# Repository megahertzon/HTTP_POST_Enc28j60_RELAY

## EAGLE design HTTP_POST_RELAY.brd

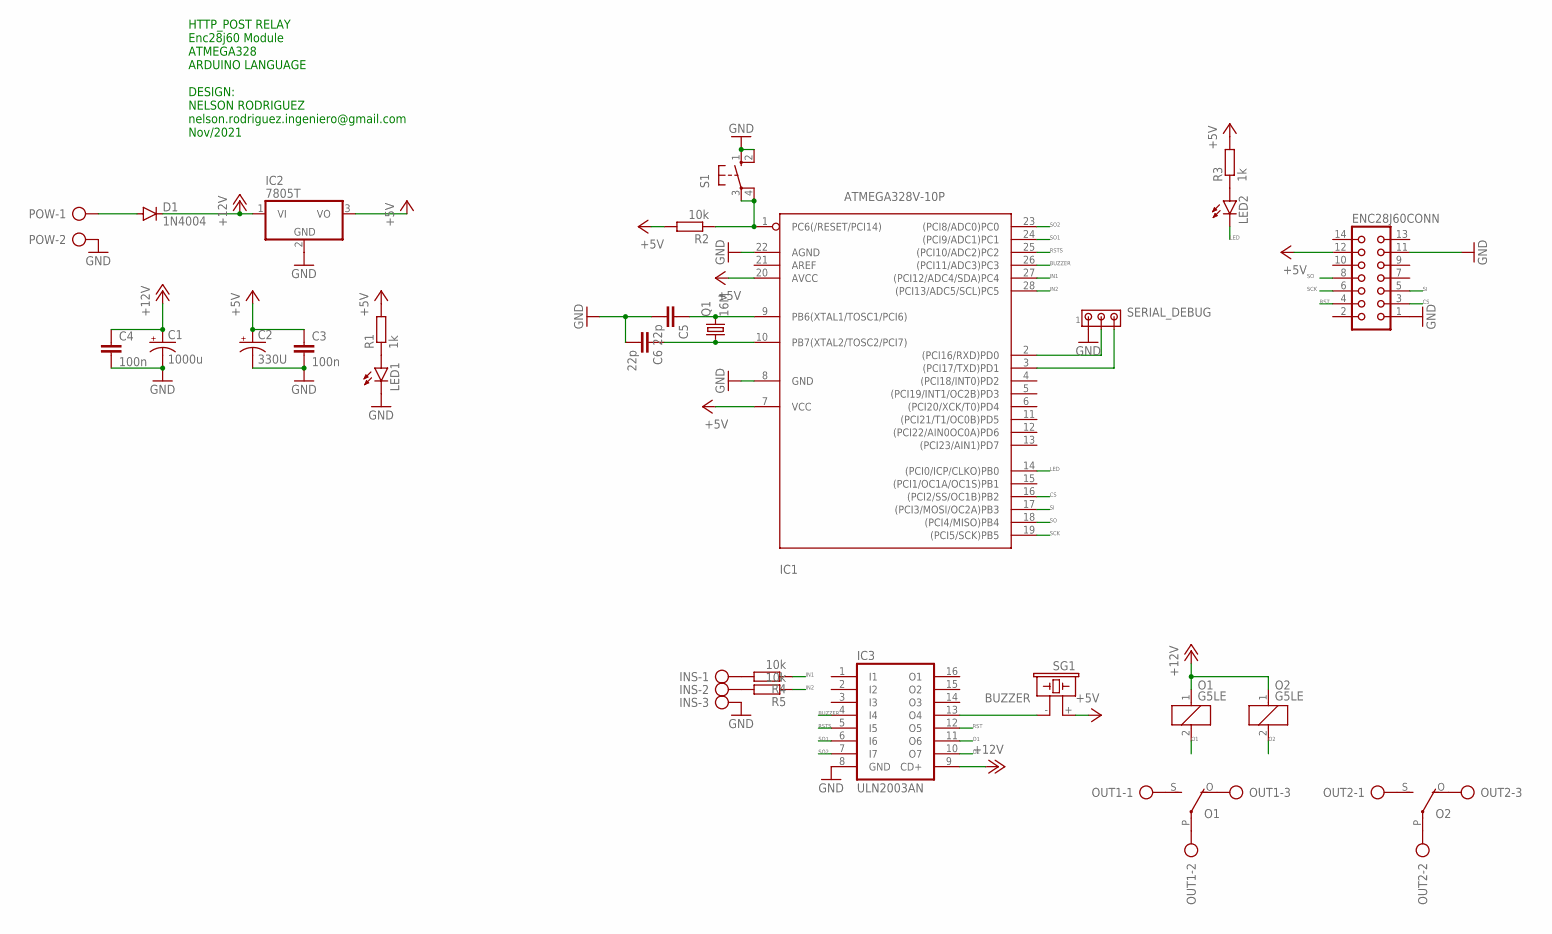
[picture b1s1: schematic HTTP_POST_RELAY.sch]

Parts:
C1: 1000u; E2,5-6
C2: 330U; E2,5-6
C3, C4: 100n; C025-024X044
C5, C6: 22p; C025-024X044
D1: 1N4004; DO41-10
ENC28J60CONN: CON14
IC1: ATMEGA328V-10P; DIL28-3
IC2: 7805T; TO220H
IC3: ULN2003AN; DIL16
INS: AK300/3
LED1, LED2: LED5MM
O1, O2: G5LE
OUT1, OUT2: AK300/3
POW: AK300/2
Q1: 16M; HC49U-V
R1, R3: 1k; 0204/7
R2, R4, R5: 10k; 0204/7
S1: 10-XX; B3F-10XX
SERIAL_DEBUG: MTA03-100; 10X03MTA
SG1: BUZZER; F/CM12P

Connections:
+5V: C2.+, C3.1, ENC28J60CONN.12, IC1.7 (VCC), IC1.20 (AVCC), IC2.3 (VO), R1.2, R2.2, R3.2, SG1.+ (1)
+12V: C1.+, C4.1, D1.C, IC2.1 (VI), IC3.9 (CD+), O1.1, O2.1
BUZZER: IC1.26 ((PCI11/ADC3)PC3), IC3.4 (I4)
CS: ENC28J60CONN.3, IC1.16 ((PCI2/SS/OC1B)PB2)
GND: C1.-, C2.-, C3.2, C4.2, C5.2, C6.2, ENC28J60CONN.1, ENC28J60CONN.11, IC1.8 (GND), IC1.22 (AGND), IC2.2 (GND), IC3.8 (GND), INS.3, LED1.K (C), POW.2, S1.1 (S), S1.2 (S1), SERIAL_DEBUG.1
IN1: IC1.27 ((PCI12/ADC4/SDA)PC4), R4.1
IN2: IC1.28 ((PCI13/ADC5/SCL)PC5), R5.1
LED: IC1.14 ((PCI0/ICP/CLKO)PB0), LED2.K (C)
unnamed: D1.A, POW.1
unnamed: LED1.A, R1.1
unnamed: C6.1, IC1.10 (PB7(XTAL2/TOSC2/PCI7)), Q1.1
unnamed: C5.1, IC1.9 (PB6(XTAL1/TOSC1/PCI6)), Q1.2
unnamed: IC1.2 ((PCI16/RXD)PD0), SERIAL_DEBUG.2
unnamed: IC1.1 (PC6(/RESET/PCI14)), R2.1, S1.3, S1.4 (P1)
unnamed: IC1.3 ((PCI17/TXD)PD1), SERIAL_DEBUG.3
unnamed: LED2.A, R3.1
unnamed: IC3.13 (O4), SG1.- (2)
unnamed: INS.1, R4.2
unnamed: INS.2, R5.2
unnamed: O1.P, OUT1.2
unnamed: O1.S, OUT1.1
unnamed: O1.O, OUT1.3
unnamed: O2.P, OUT2.2
unnamed: O2.S, OUT2.1
unnamed: O2.O, OUT2.3
O1: IC3.11 (O6), O1.2
O2: IC3.10 (O7), O2.2
RST: ENC28J60CONN.4, IC3.12 (O5)
RSTS: IC1.25 ((PCI10/ADC2)PC2), IC3.5 (I5)
SCK: ENC28J60CONN.6, IC1.19 ((PCI5/SCK)PB5)
SI: ENC28J60CONN.5, IC1.17 ((PCI3/MOSI/OC2A)PB3)
SO: ENC28J60CONN.8, IC1.18 ((PCI4/MISO)PB4)
SO1: IC1.24 ((PCI9/ADC1)PC1), IC3.6 (I6)
SO2: IC1.23 ((PCI8/ADC0)PC0), IC3.7 (I7)

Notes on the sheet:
HTTP_POST RELAY Enc28j60 Module ATMEGA328 ARDUINO LANGUAGE DESIGN: NELSON RODRIGUEZ nelson.rodriguez.ingeniero@gmail.com Nov/2021

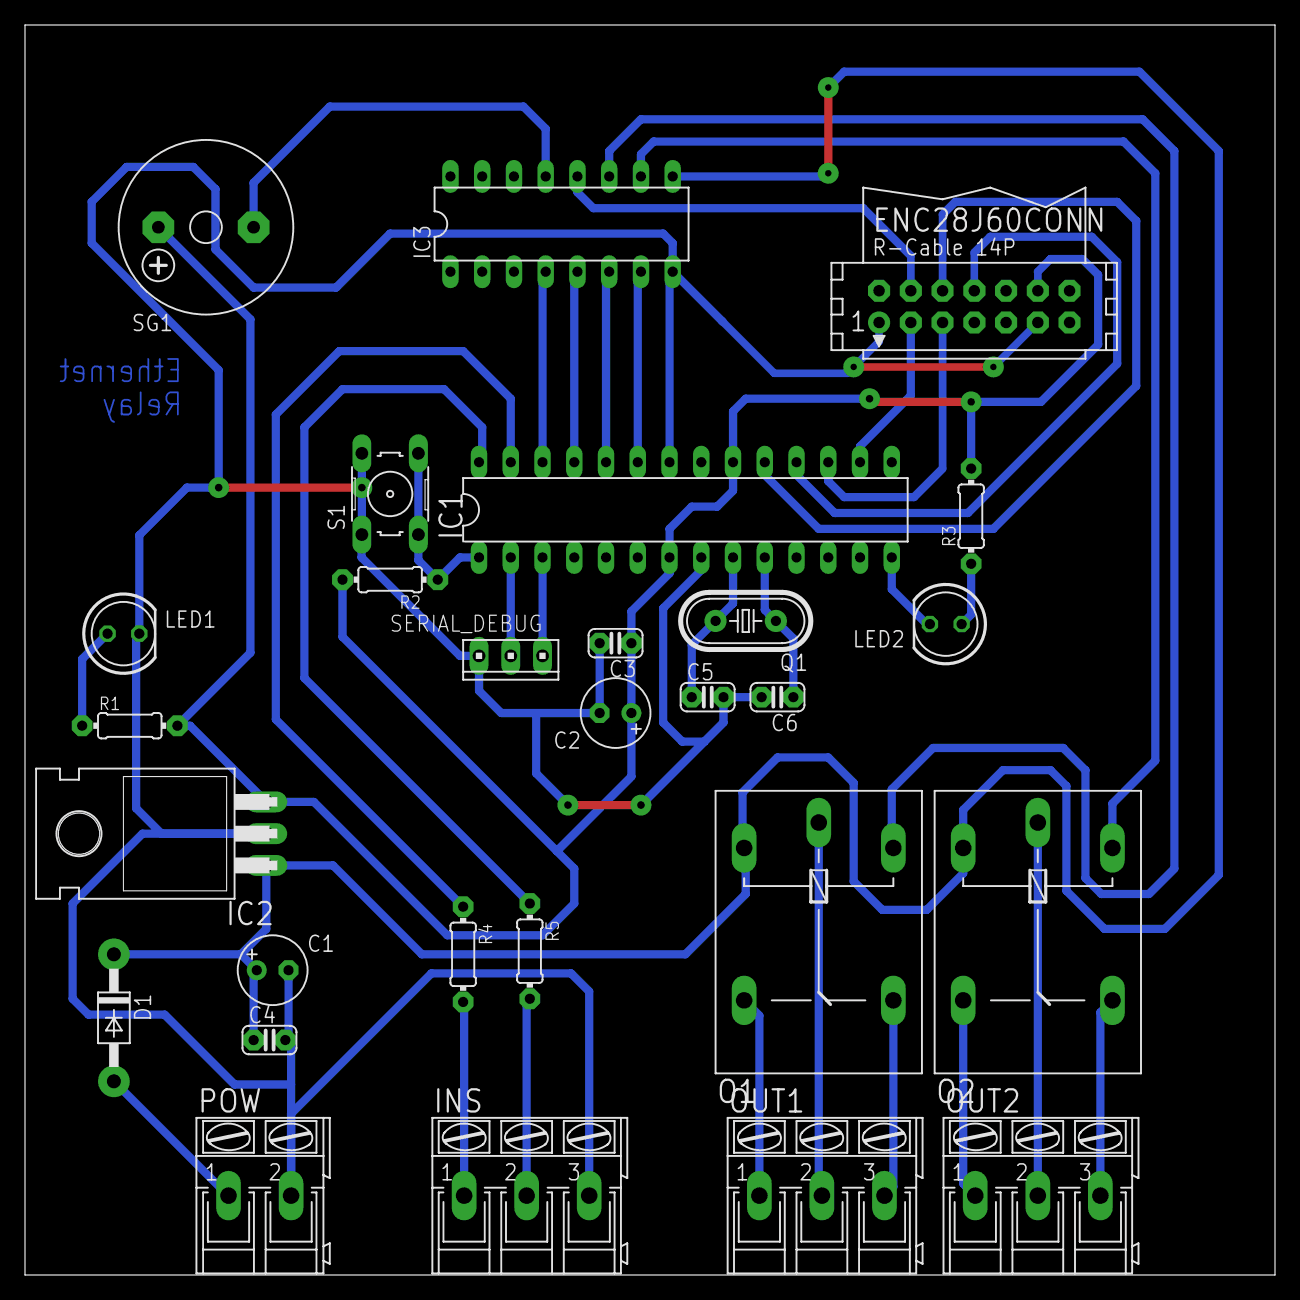
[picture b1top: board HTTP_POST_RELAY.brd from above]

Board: 2 copper layers, 100.0 x 100.0 mm, 28 parts (0 on the bottom side), 34 nets.

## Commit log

2021-11-07 create schematic and rout board
2021-11-13 add microcontroller firmware
